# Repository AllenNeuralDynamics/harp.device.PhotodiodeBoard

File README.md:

# harp.device.photodiode_board

**PhotodiodeBoard**: an RP2040-based [Harp](https://harp-tech.org/) device that samples two photodiode channels (ADC0 on GPIO27 and ADC1 on GPIO28, which are RP2040 ADC inputs 1 and 2) and streams timestamped readings to the host at 1 kHz.

* WhoAmI: `1412`
* Register definitions: [device.yml](./device.yml) (the authoritative register contract)
* Firmware build/flash instructions: [firmware/README.md](./firmware/README.md)
* Harp core library: [harp-tech/core.pico](https://github.com/harp-tech/core.pico), as a submodule pinned to commit `4654245`

## Registers
| Address | Name | Type | Access | Description |
|---|---|---|---|---|
| 32 | `ADC` | U8[2] | Event | Raw readings for ADC0 and ADC1: the top 8 bits of each 12-bit conversion (0-255). |

Events are sent at a fixed 1 kHz while the device is in Active mode (`OperationControl`) and replies are not muted. Start and stop the stream with Active/Standby. `ADC` can also be read on demand, which returns a fresh sample.

## Testing
With the device connected, run:
```
uv run software/test_adc_stream.py <port>
```
This checks identity, event rate and timestamp spacing, channel values, and that no events are sent in Standby. It uses the official [harp-tech/python](https://github.com/harp-tech/python) packages (`harp-serial`, `harp-device`).

# Github Release Conventions
Releases specify any vetted changes to the hardware or firmware.

Each release specifies:
* semantic versions of changed elements: hardware or firmware.
* SIPE part number (or part numbers if multiple are compatible)

Each hardware release includes:
* STEP file of the PCB (or link to corresponding CAD files) named with the SIPE part number
* schematic (PDF)
* Gerber files (with logos removed) of the PCBA
* Position files for component placement
* Bill-of-Materials for the PCBA

Each hardware release specifies:
* compatible SIPE part number(s)

> [!NOTE]
> SIPE part numbers only encode hardware semantic version major number, so multiple minor/patch hardware releases may point to the same SIPE part number.

> [!NOTE]
> It is possible for a project to have PCBA variants--possibly with very different functionality. In this case, reserve a hardware major version range (>100 suggested) for this variant and treat it as a distinct hardware release (i.e: with all corresponding included hardware files).

Each firmware release specifies:
* firmware semantic version
* compatible hardware (SIPE part number or part number range).

Each firmware release includes:
* compiled binary file (**\*.uf2**) of the firmware.

## Release Title
The release title is specified as follows:

`hw{hw major}.{hw minor}.{hw patch}-fw{fw major}.{fw minor}.{fw patch}`

If the release has firmware-only changes, you can drop the `hw*` section, and vice versa.

> [!NOTE]
> After Oct 2024, hardware major fields on all future releases will be equivalent to the major version number of the SIPE part number. See the [SIPE PCBA part numbering standard](https://alleninstitute.sharepoint.com/:w:/s/Instrumentation/EYsRN8q4jHJDmG5DNf-gaM0Bq418YMXollFxtB9d_NZ6pg?e=joLAvU) for more details.

The above field spec enables automation utilities to find the latest firmware version and automatically update compatible hardware. Since releases can include changes to some, but not other fields, unchanged fields are omitted. (i.e: firmware-only changes would be titled `fw{fw major}.{fw minor}.{fw patch}`.)

## Creating a New Release
1. Make a [git tag](https://git-scm.com/book/en/v2/Git-Basics-Tagging) based on the commit in the main branch that you'd like to create the release from. Use the naming convention specified in the [Release Title](#release-title) section.
2. Push the tag to Github.
3. From the repository's corresponding *Release* page, create a new release from the tag you just added. Give it the same title as the tag.
4. If the release includes new _firmware_, compile it locally, and upload a copy of the *.uf2* file as an attachment.
5. If the release includes new _hardware_, upload:
    1. the gerber files (zipped)
    2. the position files
    3. any manufacturing notes (component orientations)
    4. the bill-of-materials
    5. a PDF of the schematic.

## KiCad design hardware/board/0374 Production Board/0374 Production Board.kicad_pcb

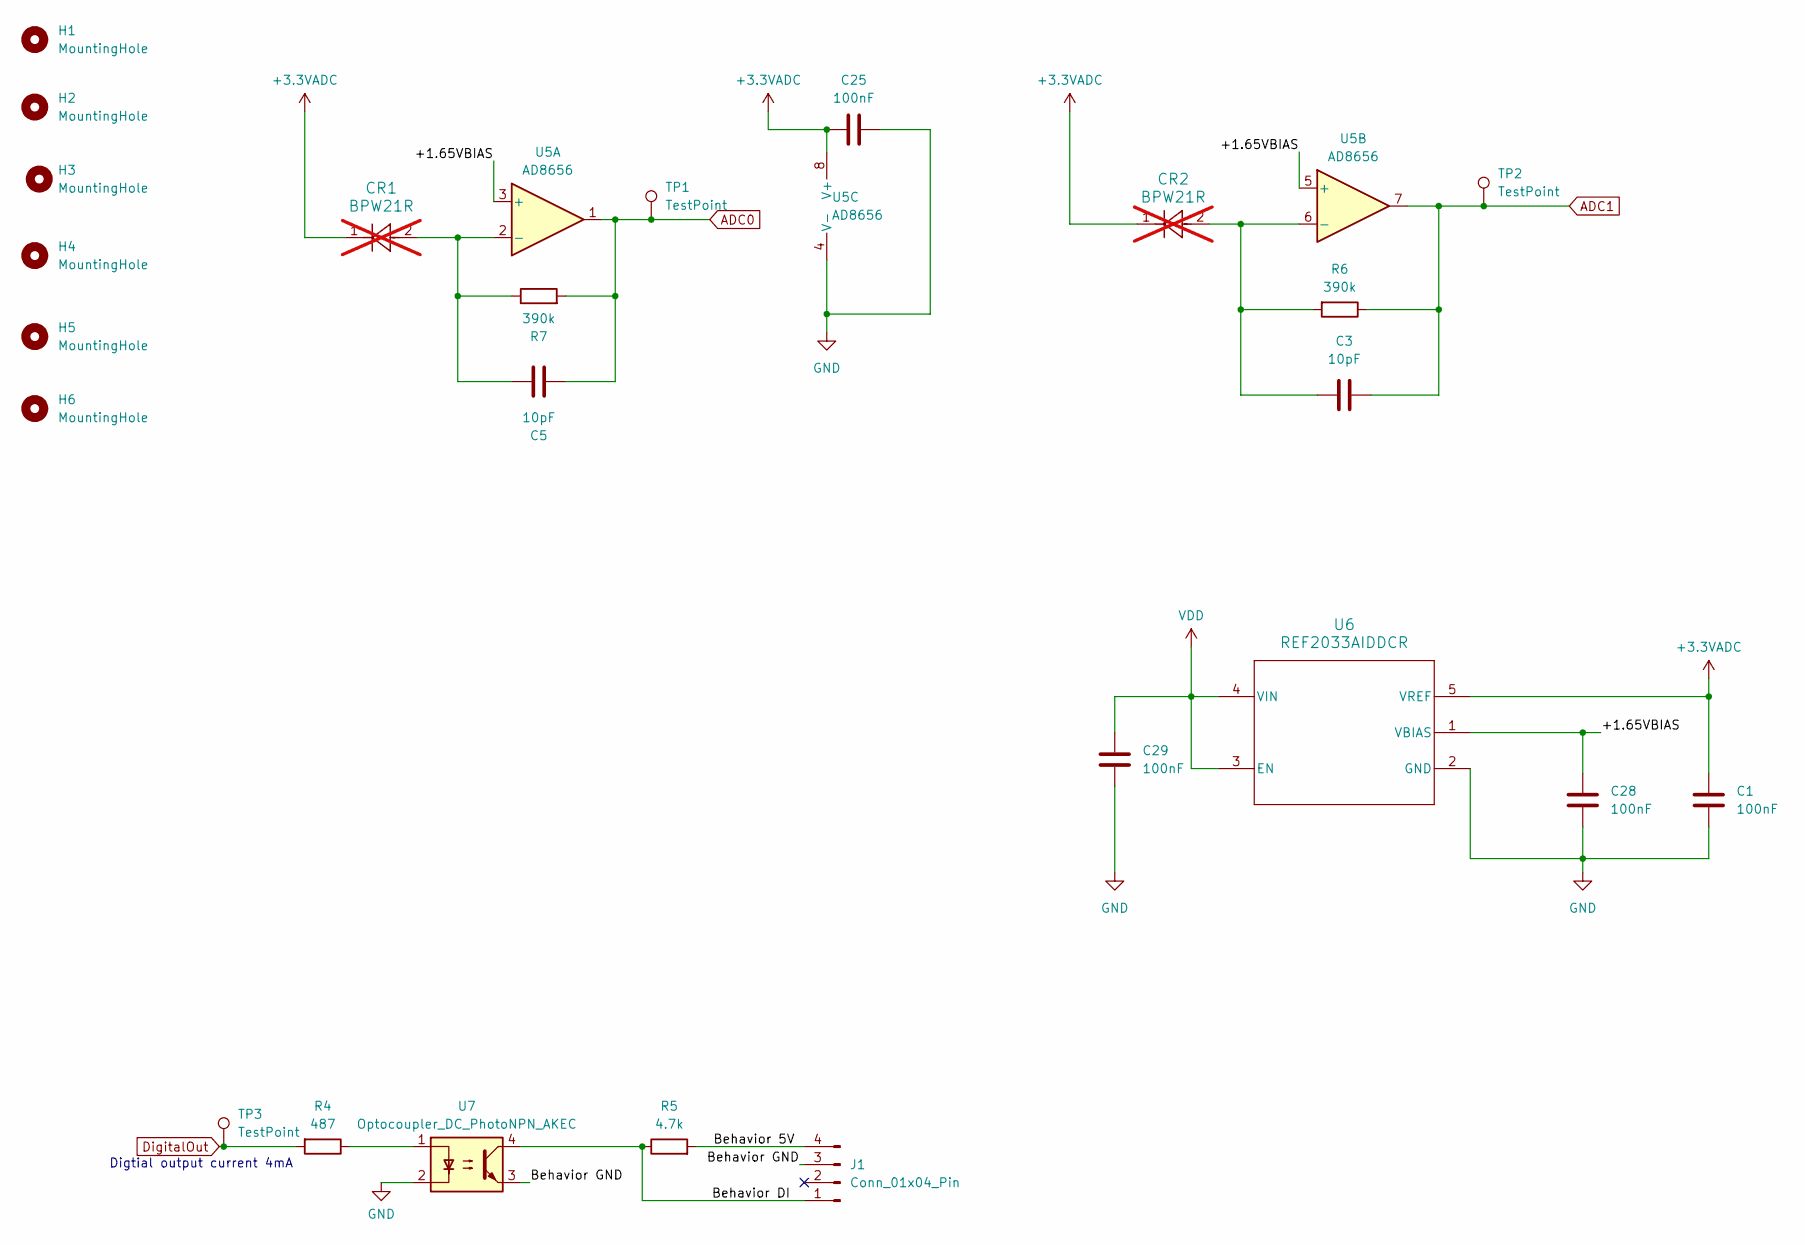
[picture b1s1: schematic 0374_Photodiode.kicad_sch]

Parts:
C1, C25, C28, C29: 100nF; C_0402_1005Metric; Rated Voltage 16V; Tolerance 10%
C3, C5: 10pF; C_0805_2012Metric_Pad1.18x1.45mm_HandSolder; Rated Voltage 50V; Tolerance 5%
CR1, CR2: BPW21R; TO99_BPW20RF_VIS; not fitted
H1, H2, H3, H4: MountingHole; MountingHole_3.2mm_M3_DIN965
H5, H6: MountingHole; MountingHole_2.2mm_M2_DIN965
J1: Conn_01x04_Pin; Connector_3M_MiniClamp_4_37204-1BE0-004PL
R4: 487; R_0402_1005Metric
R5: 4.7k; R_0402_1005Metric
R6, R7: 390k; R_0805_2012Metric_Pad1.20x1.40mm_HandSolder
TP1, TP2, TP3: TestPoint; TestPoint_Loop_D2.50mm_Drill1.0mm
U5: AD8656; R_8_ADI
U6: REF2033AIDDCR; DDC0005A_M
U7: Optocoupler_DC_PhotoNPN_AKEC; MFSOP6-4_4.4x3.6mm_P1.27mm

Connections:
+3.3VADC: C1.1, C25.1, CR1.1, CR2.1, U5.8 (V+), U6.5 (VREF); also elsewhere on the board
/PD with OP AMP + DO connection/+1.65VBIAS: C28.1, U5.3 (+), U5.5 (+), U6.1 (VBIAS)
/PD with OP AMP + DO connection/Behavior 5V: J1.4, R5.2
/PD with OP AMP + DO connection/Behavior DI: J1.1, R5.1, U7.4
/PD with OP AMP + DO connection/Behavior GND: J1.3, U7.3
ADC0: C5.1, R7.2, TP1.1, U5.1; also elsewhere on the board
ADC1: C3.1, R6.1, TP2.1, U5.7; also elsewhere on the board
DigitalOut: R4.2, TP3.1; also elsewhere on the board
GND: C1.2, C25.2, C28.2, C29.2, U5.4 (V-), U6.2 (GND), U7.2; also elsewhere on the board
unnamed: R4.1, U7.1
unnamed: C5.2, CR1.2, R7.1, U5.2 (-)
unnamed: C3.2, CR2.2, R6.2, U5.6 (-)
VDD: C29.1, U6.3 (EN), U6.4 (VIN); also elsewhere on the board

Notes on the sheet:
Digtial output current 4mA

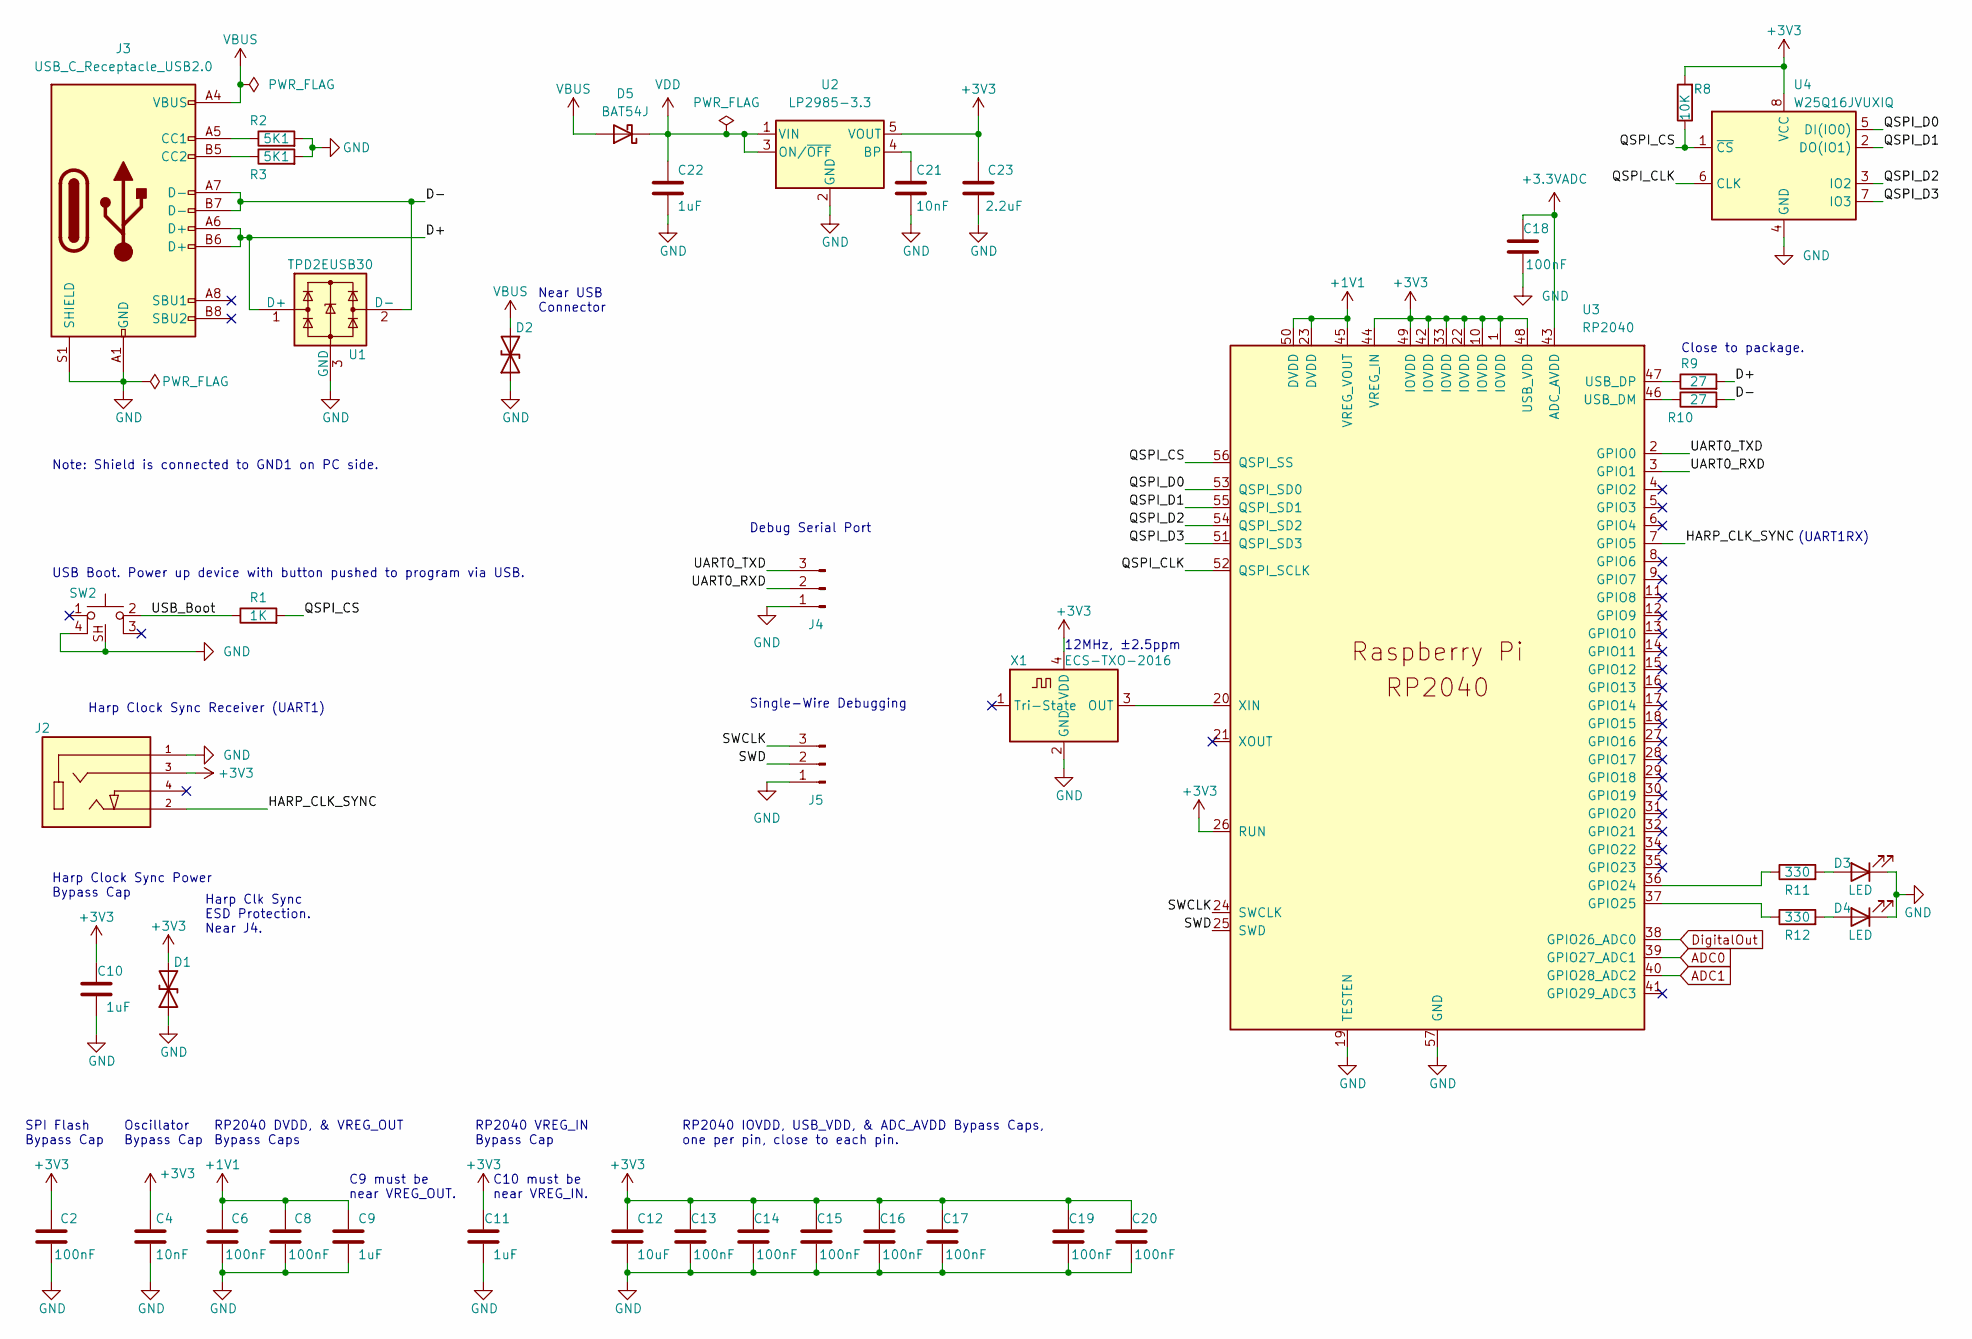
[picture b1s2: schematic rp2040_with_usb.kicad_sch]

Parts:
C2, C6, C8, C13, C14, C15, C16, C17, C18, C19, C20: 100nF; C_0402_1005Metric; Rated Voltage 16V; Tolerance 10%
C4, C21: 10nF; C_0402_1005Metric; Rated Voltage 25V; Tolerance 2%
C9, C10, C11, C22: 1uF; C_0402_1005Metric; Rated Voltage 10V; Tolerance 10%
C12: 10uF; C_0805_2012Metric; Rated Voltage 25V; Tolerance 10%
C23: 2.2uF; C_0402_1005Metric; Rated Voltage 10V; Tolerance 10%
D1, D2: D_TVS; D_0201_0603Metric
D3, D4: LED; LED_0603_1608Metric_Pad1.05x0.95mm_HandSolder
D5: BAT54J; D_SOD-323F
J2: AudioJack3; CUI_SJ-3524-SMT-BE
J3: USB_C_Receptacle_USB2.0; USB_C_Receptacle_JAE_DX07S016JA1R1500
J4, J5: PinHeader_1x03_P2.54mm_Vertical
R1: 1K; R_0402_1005Metric; Tolerance 1%
R2, R3: 5K1; R_0402_1005Metric; Tolerance 1%
R8: 10K; R_0402_1005Metric; Tolerance 1%
R9, R10: 27; R_0402_1005Metric; Tolerance 1%
R11, R12: 330; R_0402_1005Metric; Tolerance 0.1%
SW2: 435451019820
U1: TPD2EUSB30; Texas_DRT-3
U2: LP2985-3.3; SOT-23-5
U3: RP2040; QFN56_7X7_RPI
U4: W25Q16JVUXIQ; USON-8_UX_2x3x0p6_WIN
X1: ECS-TXO-2016; Crystal_SMD_2016-4Pin_2.0x1.6mm; Tolerance ±2.5ppm

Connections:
+1V1: C6.2, C8.2, C9.1, U3.23 (DVDD), U3.45 (VREG_VOUT), U3.50 (DVDD)
+3.3VADC: C18.2, U3.43 (ADC_AVDD); also elsewhere on the board
+3V3: C2.2, C4.1, C10.1, C11.1, C12.1, C13.2, C14.2, C15.2, C16.2, C17.2, C19.2, C20.2, C23.2, D1.2 (A2), J2.3, R8.2, U2.5 (VOUT), U3.1 (IOVDD), U3.10 (IOVDD), U3.22 (IOVDD), U3.26 (RUN), U3.33 (IOVDD), U3.42 (IOVDD), U3.44 (VREG_IN), U3.48 (USB_VDD), U3.49 (IOVDD), U4.8 (VCC), X1.4 (VDD)
/Harp Core RP2040 + USB/D+: J3.A6 (D+), J3.B6 (D+), R9.2, U1.1 (D+)
/Harp Core RP2040 + USB/D-: J3.A7 (D-), J3.B7 (D-), R10.2, U1.2 (D-)
/Harp Core RP2040 + USB/HARP_CLK_SYNC: J2.2, U3.7 (GPIO5)
/Harp Core RP2040 + USB/QSPI_CLK: U3.52 (QSPI_SCLK), U4.6 (CLK)
/Harp Core RP2040 + USB/QSPI_CS: R1.2, R8.1, U3.56 (QSPI_SS), U4.1 (~CS)
/Harp Core RP2040 + USB/QSPI_D0: U3.53 (QSPI_SD0), U4.5 (DI(IO0))
/Harp Core RP2040 + USB/QSPI_D1: U3.55 (QSPI_SD1), U4.2 (DO(IO1))
/Harp Core RP2040 + USB/QSPI_D2: U3.54 (QSPI_SD2), U4.3 (IO2)
/Harp Core RP2040 + USB/QSPI_D3: U3.51 (QSPI_SD3), U4.7 (IO3)
/Harp Core RP2040 + USB/SWCLK: J5.3, U3.24 (SWCLK)
/Harp Core RP2040 + USB/SWD: J5.2, U3.25 (SWD)
/Harp Core RP2040 + USB/UART0_RXD: J4.2, U3.3 (GPIO1)
/Harp Core RP2040 + USB/UART0_TXD: J4.3, U3.2 (GPIO0)
/Harp Core RP2040 + USB/USB_Boot: R1.1, SW2.2
ADC0: U3.39 (GPIO27_ADC1); also elsewhere on the board
ADC1: U3.40 (GPIO28_ADC2); also elsewhere on the board
DigitalOut: U3.38 (GPIO26_ADC0); also elsewhere on the board
GND: C2.1, C4.2, C6.1, C8.1, C9.2, C10.2, C11.2, C12.2, C13.1, C14.1, C15.1, C16.1, C17.1, C18.1, C19.1, C20.1, C21.2, C22.2, C23.1, D1.1 (A1), D2.1 (A1), D3.1 (K), D4.1 (K), J2.1, J3.A1 (GND), J3.A12 (GND), J3.B1 (GND), J3.B12 (GND), J3.S1 (SHIELD), J4.1, J5.1, R2.2, R3.2, SW2.4, SW2.SH, U1.3 (GND), U2.2 (GND), U3.19 (TESTEN), U3.57 (GND), U4.4 (GND), X1.2 (GND); also elsewhere on the board
unnamed: D3.2 (A), R11.2
unnamed: D4.2 (A), R12.2
unnamed: J3.A5 (CC1), R2.1
unnamed: J3.B5 (CC2), R3.1
unnamed: C21.1, U2.4 (BP)
unnamed: R11.1, U3.36 (GPIO24)
unnamed: R12.1, U3.37 (GPIO25)
unnamed: R10.1, U3.46 (USB_DM)
unnamed: R9.1, U3.47 (USB_DP)
unnamed: U3.20 (XIN), X1.3 (OUT)
VBUS: D2.2 (A2), D5.2 (A), J3.A4 (VBUS), J3.A9 (VBUS), J3.B4 (VBUS), J3.B9 (VBUS)
VDD: C22.1, D5.1 (K), U2.1 (VIN), U2.3 (ON/~OFF); also elsewhere on the board

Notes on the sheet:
C10 must be near VREG_IN.
C9 must be near VREG_OUT.
SPI Flash Bypass Cap
Close to package.
Harp Clock Sync Power Bypass Cap
Harp Clock Sync Receiver (UART1)
Oscillator Bypass Cap
RP2040 DVDD, & VREG_OUT Bypass Caps
RP2040 VREG_IN Bypass Cap
USB Boot. Power up device with button pushed to program via USB.
(UART1RX)
RP2040 IOVDD, USB_VDD, & ADC_AVDD Bypass Caps, one per pin, close to each pin.
Near USB Connector
Note: Shield is connected to GND1 on PC side.
12MHz, ±2.5ppm
Harp Clk Sync ESD Protection. Near J4.
Debug Serial Port
Single-Wire Debugging

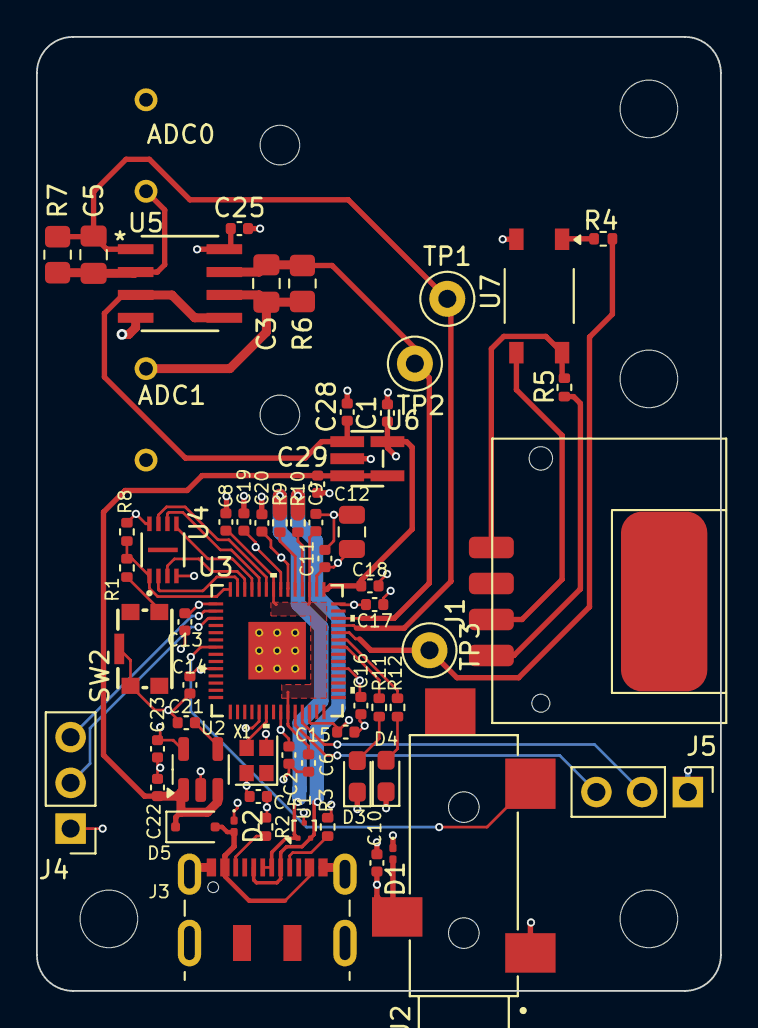
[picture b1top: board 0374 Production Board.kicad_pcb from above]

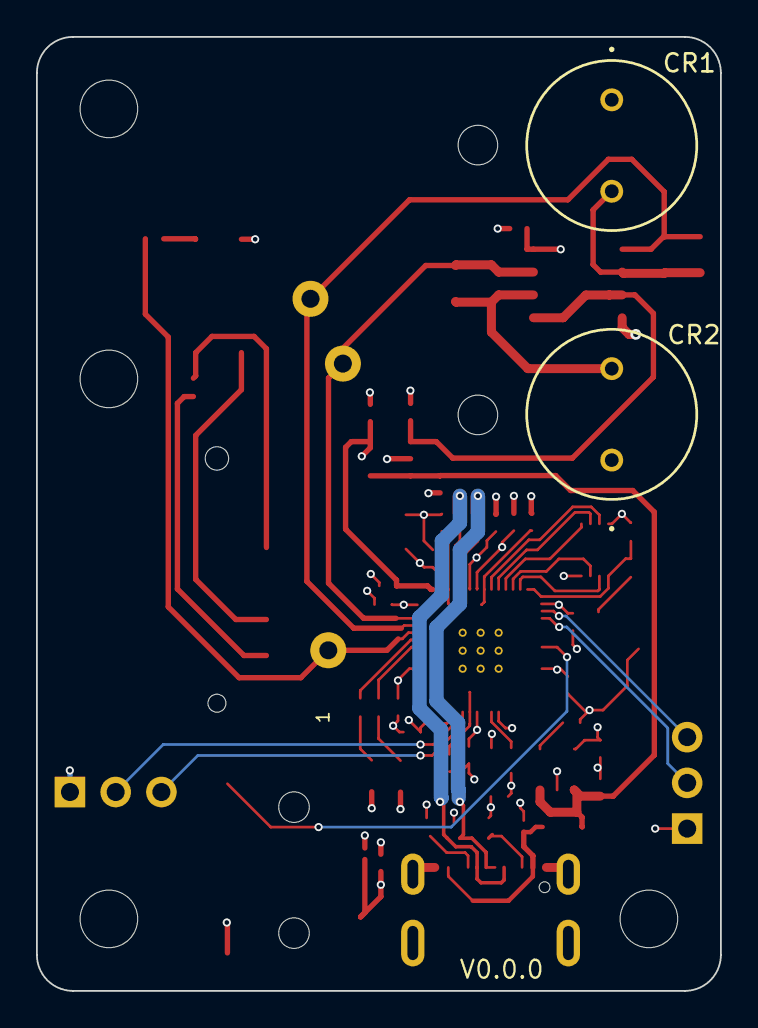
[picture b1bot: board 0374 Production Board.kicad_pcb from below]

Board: 4 copper layers, 38.0 x 53.0 mm, 67 parts (2 on the bottom side), 40 nets.

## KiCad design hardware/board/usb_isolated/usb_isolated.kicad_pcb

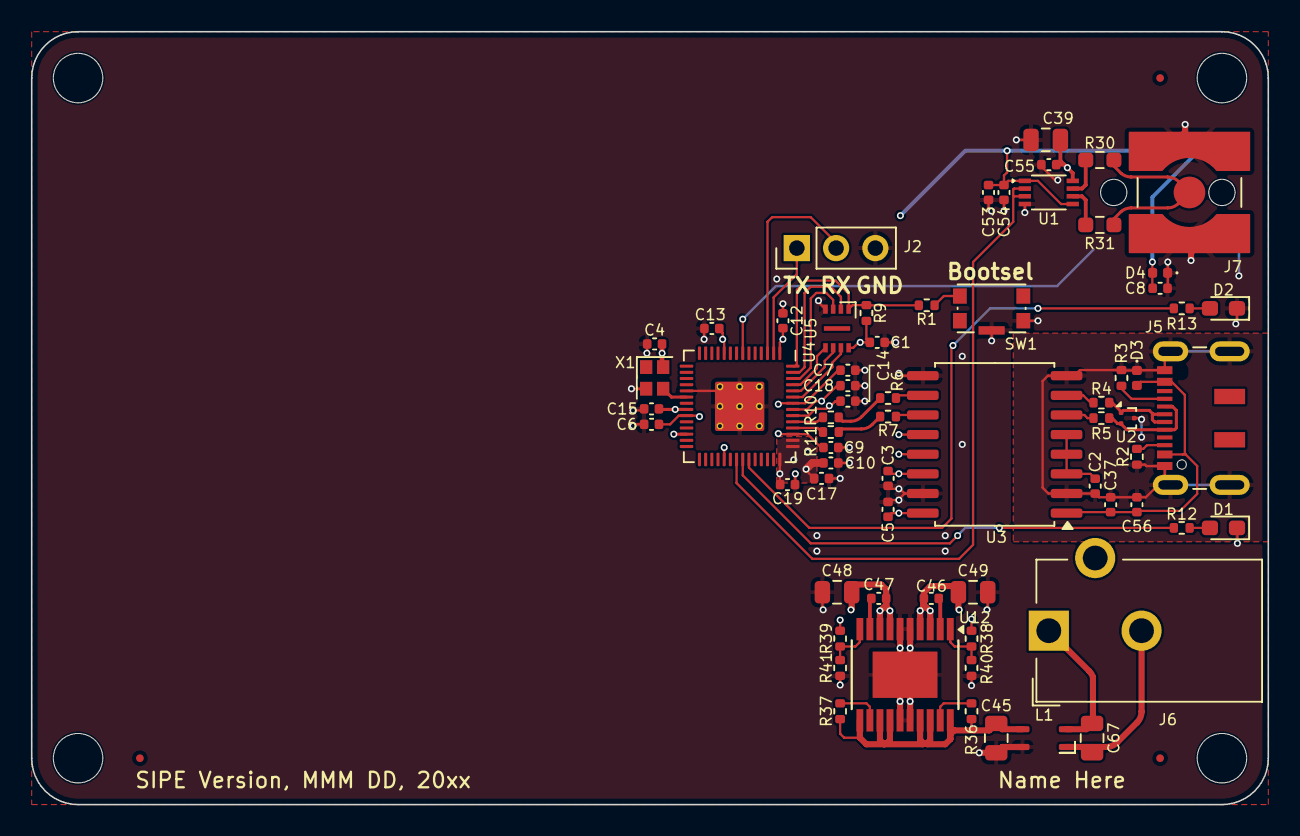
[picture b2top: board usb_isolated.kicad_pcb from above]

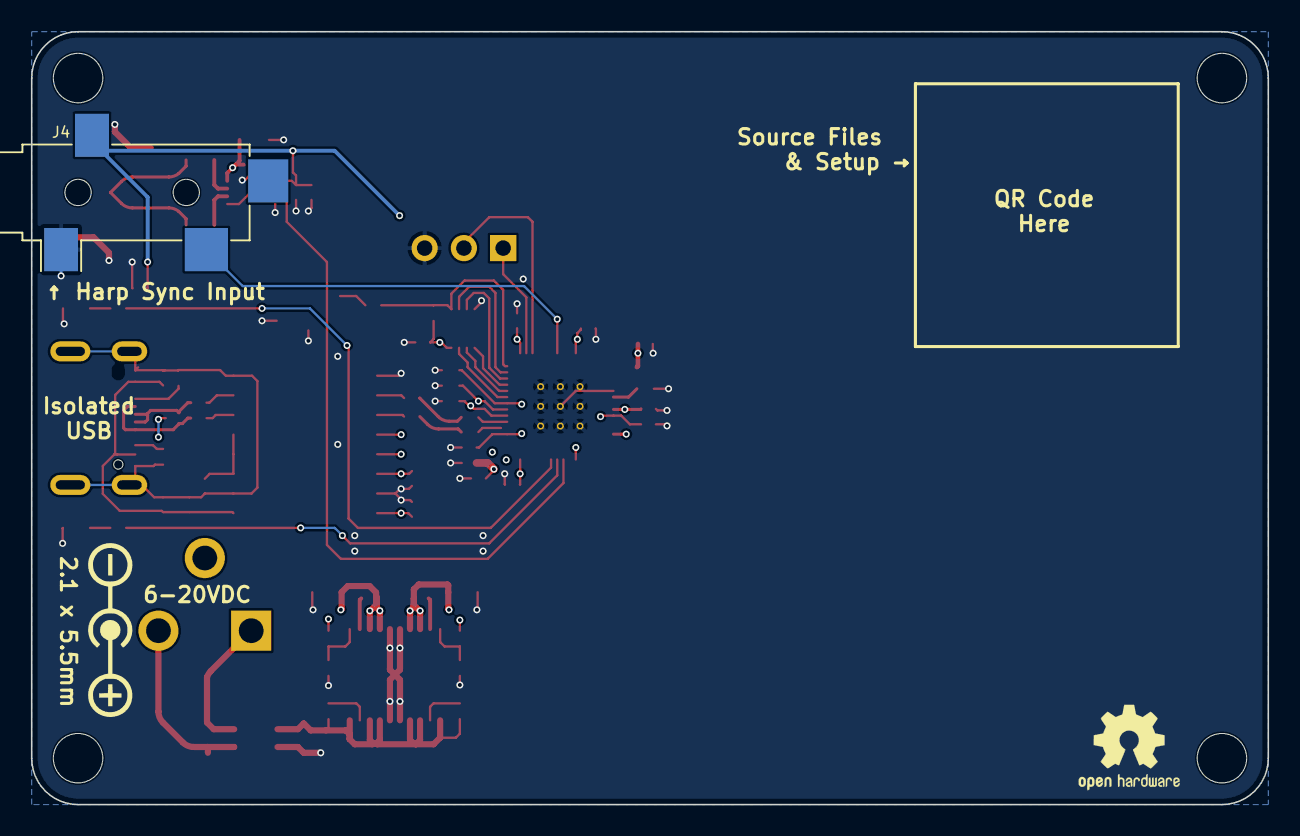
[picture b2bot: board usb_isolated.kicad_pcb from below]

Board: 4 copper layers, 80.0 x 50.0 mm, 72 parts (3 on the bottom side), 47 nets.

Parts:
C1, C2, C3, C5, C6, C7, C12, C13, C14, C15, C17, C18, C19, C37, C54, C55: 100nF; C_0402_1005Metric
C4, C46, C47: 10nF; C_0402_1005Metric
C8, C9, C10, C53, C56: 1uF; C_0402_1005Metric
C39, C48: 10uF; C_0805_2012Metric
C45, C67: 3.3uF; C_0805_2012Metric
C49: 22uF; C_0805_2012Metric
D1, D2: LED; LED_0603_1608Metric_Pad1.05x0.95mm_HandSolder
D3, D4: D_TVS; D_0402_1005Metric
FID1, FID2, FID3: Fiducial; Fiducial_0.5mm_Mask1mm
G3: LOGO
J2: Conn_01x03_Male; PinHeader_1x03_P2.54mm_Vertical
J4: AudioJack3; Jack_3.5mm_CUI_SJ-3524-SMT_Horizontal
J5: USB_C_Receptacle_USB2.0; USB_C_Receptacle_JAE_DX07S016JA1R1500
J6: Barrel_Jack_Switch; BarrelJack_CUI_PJ-102AH_Horizontal
J7: Conn_Coaxial; SMA_TE_Connectivity_CONSMA002-SMD-G-T_Horizontal
L1: L_Coupled_1423; L_CommonModeChoke_TDKCorporation_1210
R1: 1K; R_0402_1005Metric
R2, R3: 5K1; R_0402_1005Metric
R4, R5, R6, R7: 24; R_0402_1005Metric
R9: 10K; R_0402_1005Metric
R10, R11: 27; R_0402_1005Metric
R12, R13: 680; R_0402_1005Metric
R30, R31: 100; R_0603_1608Metric_Pad0.98x0.95mm_HandSolder
R36, R37: 1M; R_0402_1005Metric
R38: 309K; R_0402_1005Metric
R39: 172K; R_0402_1005Metric
R40, R41: 100K; R_0402_1005Metric
REF1: OSHW-Logo2_7.3x6mm_SilkScreen
SW1: SW_Push_1P1T-SH_NO_Vertical_Wuerth_WS-TASV
U1: 74LVCH2T45DC; VSSOP-8_2.3x2mm_P0.5mm
U2: TPD2EUSB30; Texas_DRT-3
U3: ADUM4160; SOIC-16W_7.5x10.3mm_P1.27mm
U4: RP2040; RP2040-QFN-56
U5: W25Q16JVUXIQ; Winbond-8USON-2x3mm
U12: LT3030; ETSSOP-20-1EP_4.4x6.5mm_P0.65mm_EP3x4.2mm
X1: ECS-TXO-2016; Crystal_SMD_2016-4Pin_2.0x1.6mm

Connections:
+1V1: C6.2, C7.2, C9.1, U4.23 (DVDD), U4.45 (VREG_VOUT), U4.50 (DVDD)
+3.3V: C1.2, C3.2, C4.2, C5.2, C8.1, C10.1, C12.2, C13.2, C14.2, C15.2, C17.2, C18.2, C19.2, C47.1, C48.1, C53.1, C54.2, D4.2 (A2), J4.R, R9.2, R39.1, U1.1 (VCCA), U1.5 (DIR), U3.12 (PIN), U3.13 (SPD), U3.14 (VDD2), U3.16 (VBUS2), U4.1 (IOVDD), U4.10 (IOVDD), U4.22 (IOVDD), U4.26 (RUN), U4.33 (IOVDD), U4.42 (IOVDD), U4.43 (ADC_AVDD), U4.44 (VREG_IN), U4.48 (USB_VDD), U4.49 (IOVDD), U5.8 (VCC), U12.7 (OUT2), U12.8 (OUT2), X1.4 (VDD)
+5V: C39.1, C46.1, C49.1, C55.2, R38.1, U1.8 (VCCB), U12.3 (OUT1), U12.4 (OUT1)
+12V: C67.1, J6.1, L1.2
/Harp Core RP2040 + Isolated USB/D+: J5.A6 (D+), J5.B6 (D+), R4.1, U2.1 (D+)
/Harp Core RP2040 + Isolated USB/D-: J5.A7 (D-), J5.B7 (D-), R5.1, U2.2 (D-)
/Harp Core RP2040 + Isolated USB/DD+: R6.2, R10.2
/Harp Core RP2040 + Isolated USB/DD-: R7.2, R11.2
/Harp Core RP2040 + Isolated USB/HARP_CLK_SYNC: J4.T, U4.7 (GPIO5)
/Harp Core RP2040 + Isolated USB/QSPI_CLK: U4.52 (QSPI_SCLK), U5.6 (CLK)
/Harp Core RP2040 + Isolated USB/QSPI_CS: R1.2, R9.1, U4.56 (QSPI_SS), U5.1 (~CS)
/Harp Core RP2040 + Isolated USB/QSPI_D0: U4.53 (QSPI_SD0), U5.5 (DI(IO0))
/Harp Core RP2040 + Isolated USB/QSPI_D1: U4.55 (QSPI_SD1), U5.2 (DO(IO1))
/Harp Core RP2040 + Isolated USB/QSPI_D2: U4.54 (QSPI_SD2), U5.3 (IO2)
/Harp Core RP2040 + Isolated USB/QSPI_D3: U4.51 (QSPI_SD3), U5.7 (IO3)
/Harp Core RP2040 + Isolated USB/TTL_OUT: U1.2 (1A), U1.3 (2A), U4.35 (GPIO23)
/Harp Core RP2040 + Isolated USB/UART0_RXD: J2.2, U4.3 (GPIO1)
/Harp Core RP2040 + Isolated USB/UART0_TXD: J2.1, U4.2 (GPIO0)
/Harp Core RP2040 + Isolated USB/USB_Boot: R1.1, SW1.2
/Harp Core RP2040 + Isolated USB/VDD1: C2.2, U3.3 (VDD1), U3.4 (PDEN), U3.5 (SPU)
GND: C1.1, C3.1, C4.1, C5.1, C6.1, C7.1, C8.2, C9.2, C10.2, C12.1, C13.1, C14.1, C15.1, C17.1, C18.1, C19.1, C39.2, C45.2, C48.2, C49.2, C53.2, C54.1, C55.1, D1.1 (K), D2.1 (K), D4.1 (A1), J2.3, J4.S, J7.2 (Ext), L1.4, R40.1, R41.1, SW1.4, SW1.SH, U1.4 (GND), U3.9 (GND2), U3.15 (GND2), U4.19 (TESTEN), U4.57 (GND), U5.4 (GND), U12.5 (GND), U12.6 (GND), U12.15 (GND), U12.16 (GND), U12.21 (GND), X1.2 (GND)
GND1: C2.1, C37.1, C56.2, D3.1 (A1), J5.A1 (GND), J5.A12 (GND), J5.B1 (GND), J5.B12 (GND), J5.S1 (SHIELD), R2.2, R3.2, U2.3 (GND), U3.2 (GND1), U3.8 (GND1)
GND2: C67.2, J6.2, L1.1
IN1: C45.1, L1.3, R36.1, R37.1, U12.11 (~SHDN2), U12.13 (IN2), U12.14 (IN2), U12.17 (IN1), U12.18 (IN1), U12.20 (~SHDN1)
unnamed: D1.2 (A), R12.2
unnamed: D2.2 (A), R13.2
unnamed: J5.A5 (CC1), R2.1
unnamed: J5.B5 (CC2), R3.1
unnamed: J7.1 (In), R30.2, R31.2
unnamed: R30.1, U1.7 (1B)
unnamed: R31.1, U1.6 (2B)
unnamed: R6.1, U3.10 (DD+)
unnamed: R7.1, U3.11 (DD-)
unnamed: R4.2, U3.7 (UD+)
unnamed: R5.2, U3.6 (UD-)
unnamed: R12.1, U4.36 (GPIO24)
unnamed: R13.1, U4.37 (GPIO25)
unnamed: R11.1, U4.46 (USB_DM)
unnamed: R10.1, U4.47 (USB_DP)
unnamed: U4.20 (XIN), X1.3 (OUT)
unnamed: R38.2, R40.2, U12.1 (ADJ1)
unnamed: R39.2, R41.2, U12.10 (ADJ2)
unnamed: C46.2, U12.2 (BYP1)
unnamed: C47.2, U12.9 (BYP2)
unnamed: R36.2, U12.19 (PWRGD1)
unnamed: R37.2, U12.12 (PWRGD2)
VBUS: C37.2, C56.1, D3.2 (A2), J5.A4 (VBUS), J5.A9 (VBUS), J5.B4 (VBUS), J5.B9 (VBUS), U3.1 (VBUS1)
